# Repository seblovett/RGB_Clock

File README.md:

RGB_Clock
=========

A LED Clock

A contained PCB clock, with 60 RGB LEDs to display the time. 

Includes a noise sensor, LDR to adjust the brightness.

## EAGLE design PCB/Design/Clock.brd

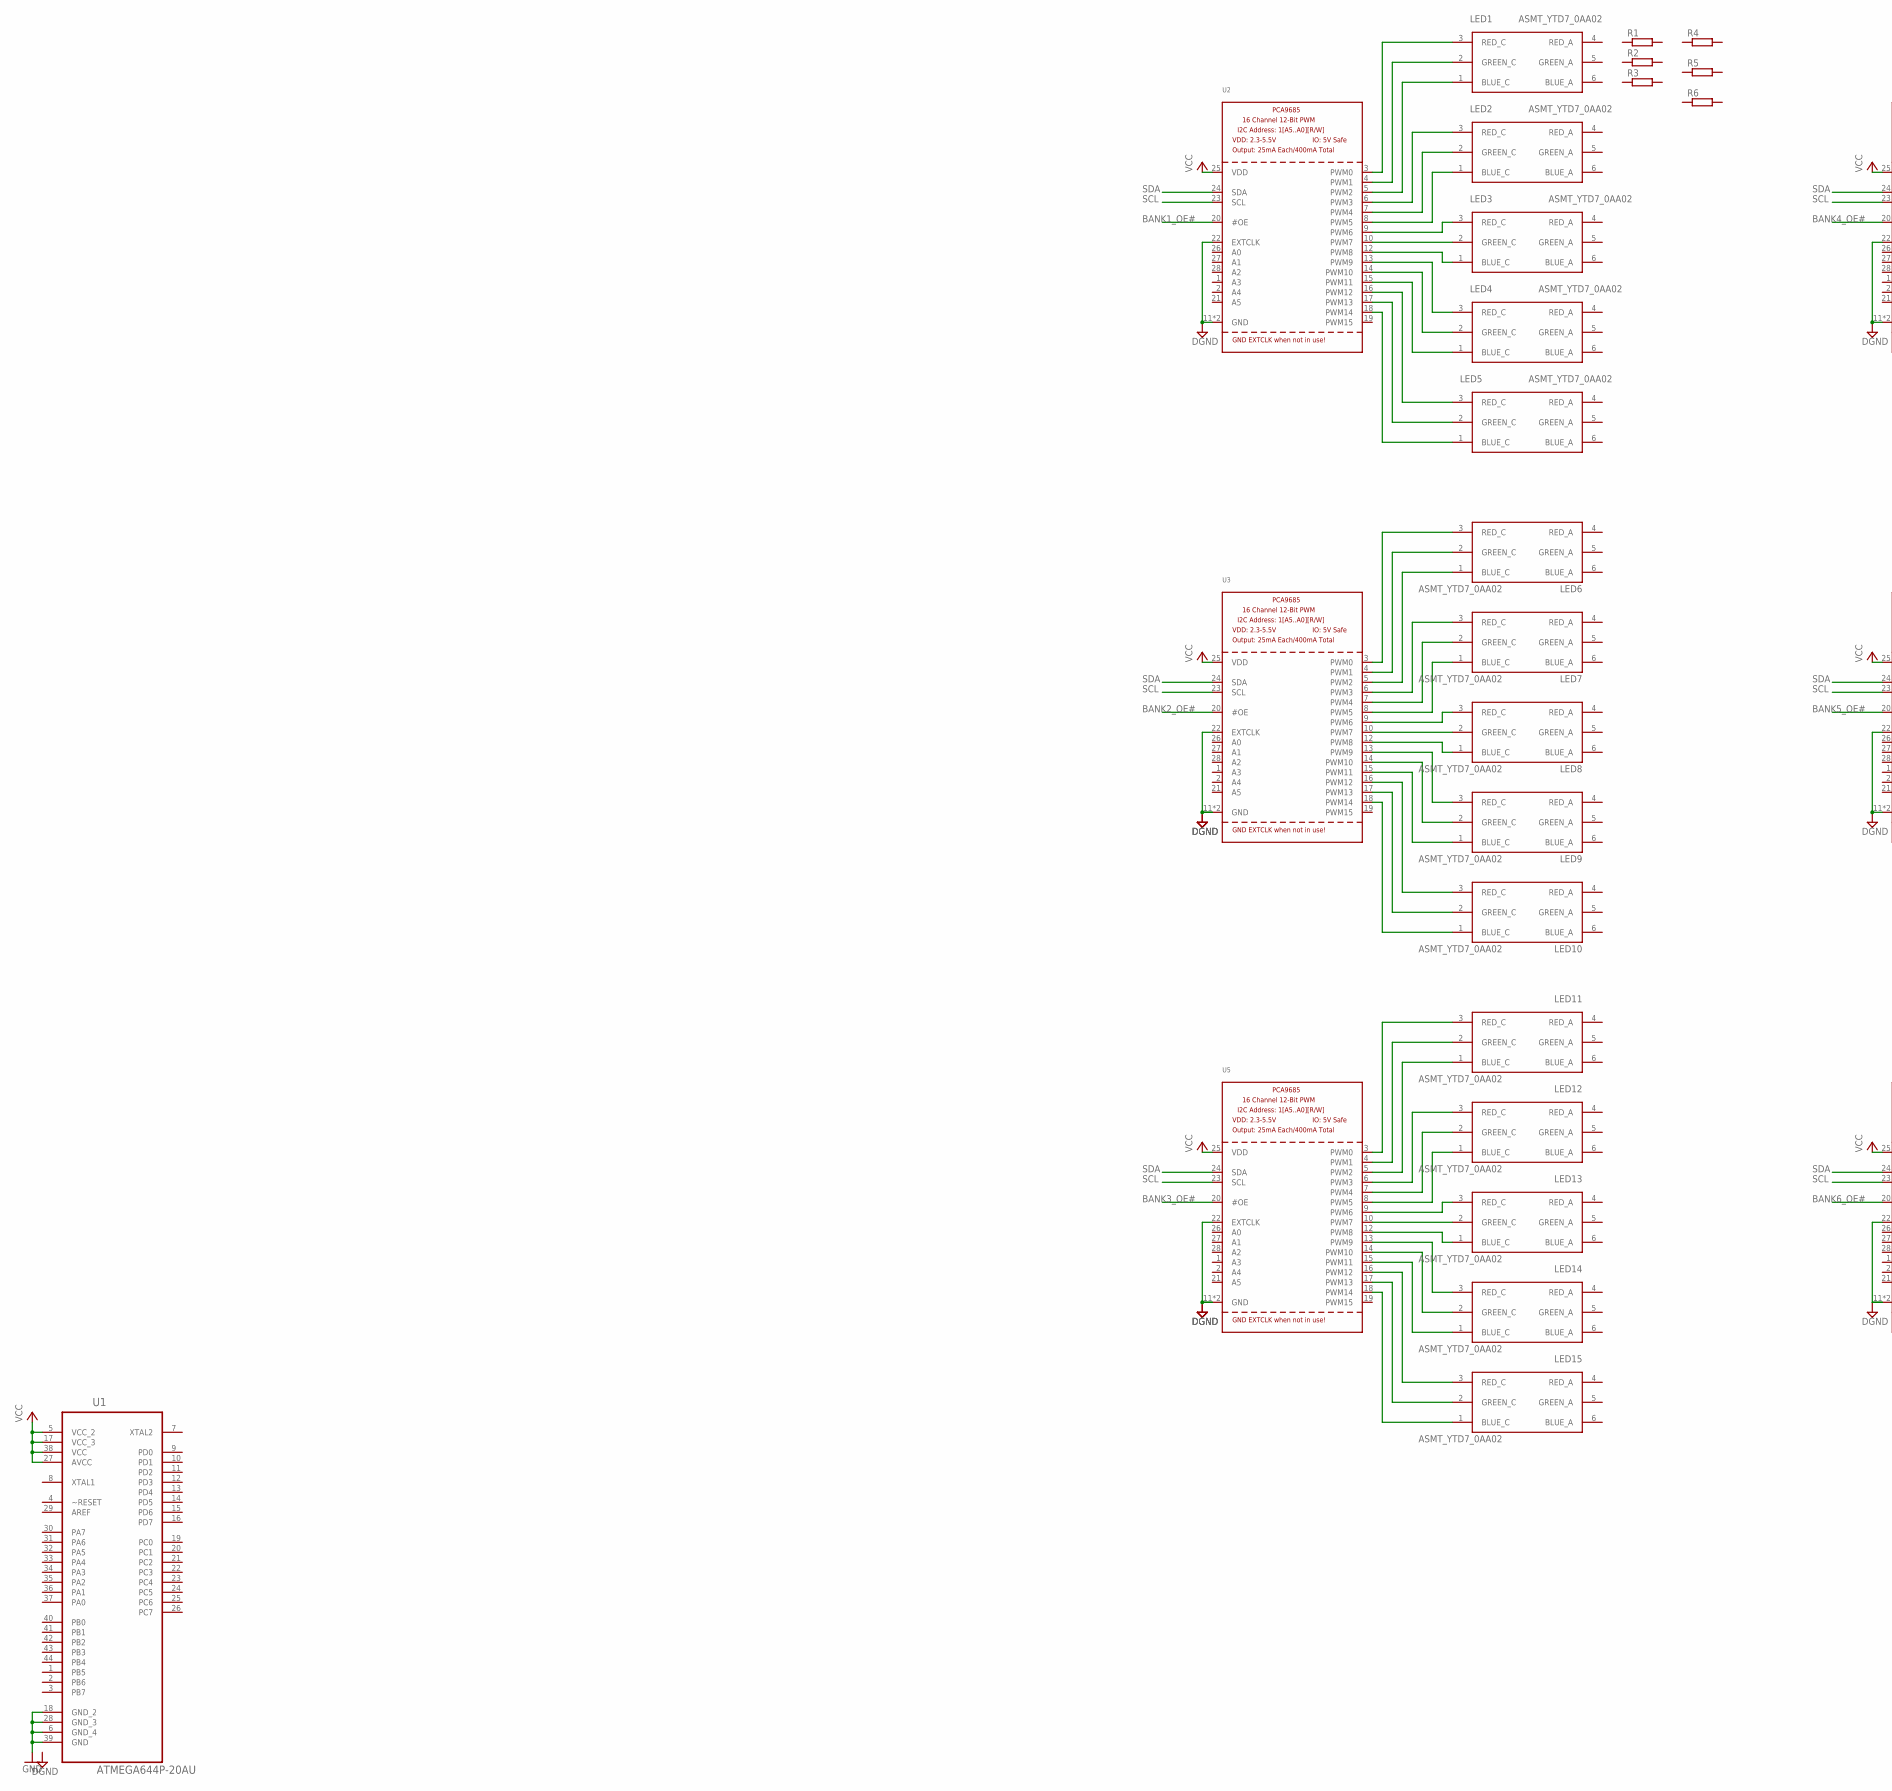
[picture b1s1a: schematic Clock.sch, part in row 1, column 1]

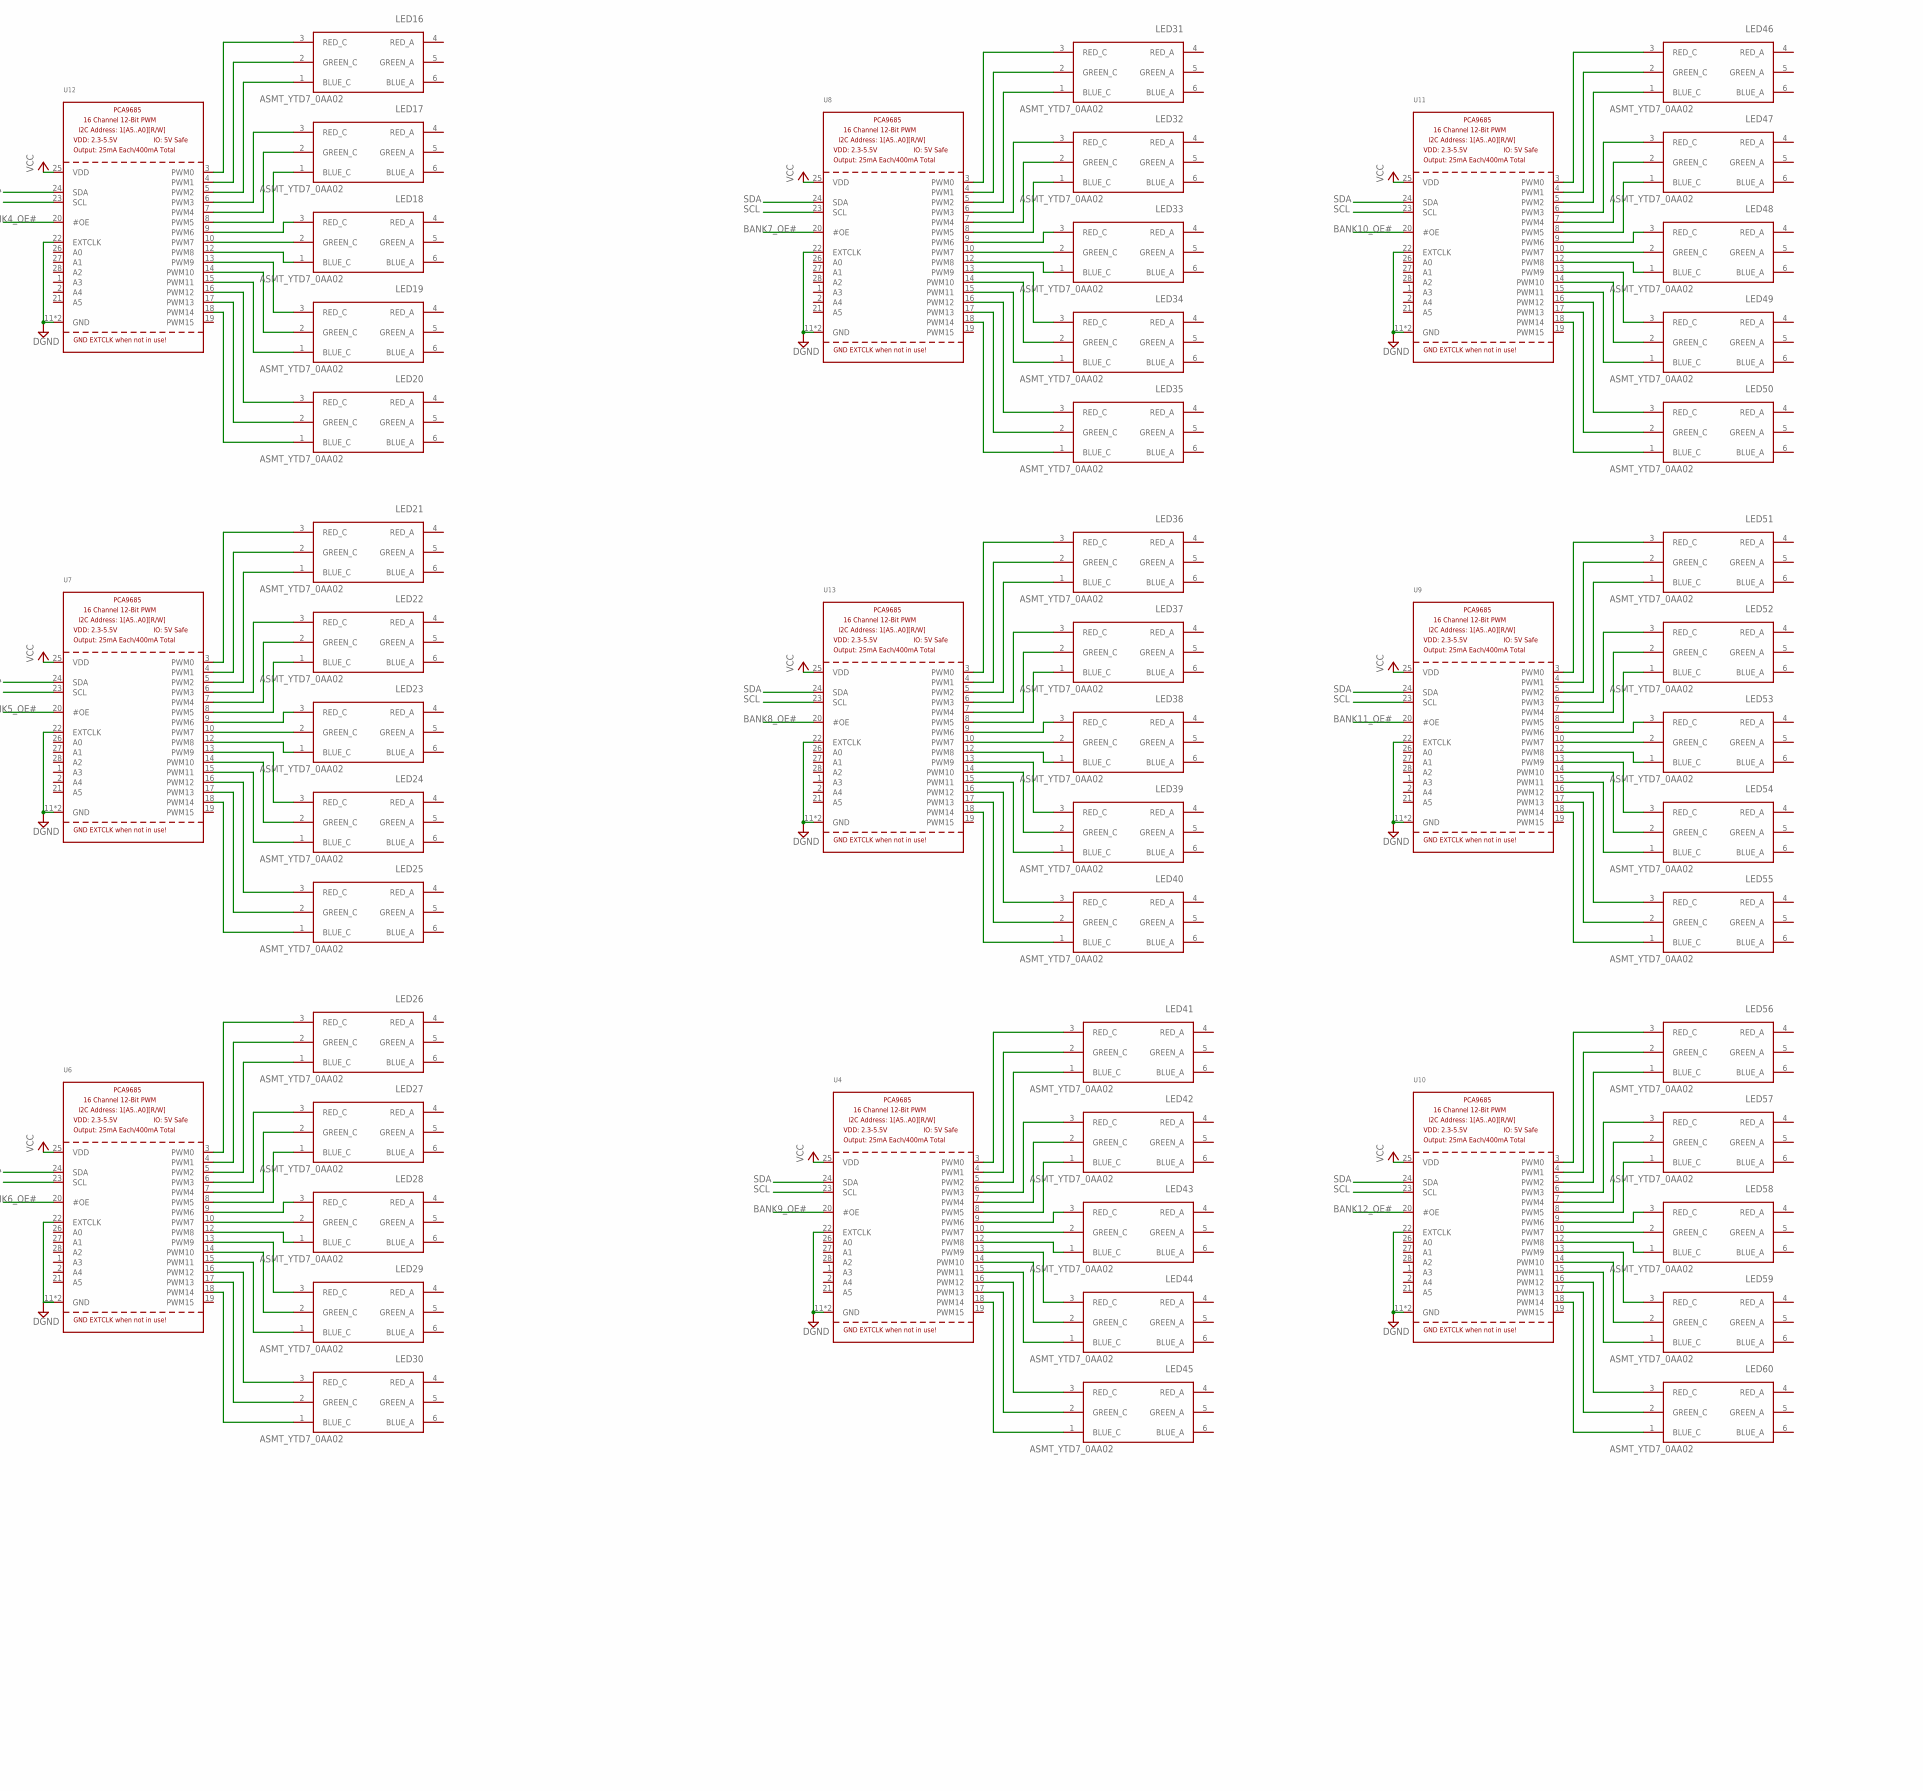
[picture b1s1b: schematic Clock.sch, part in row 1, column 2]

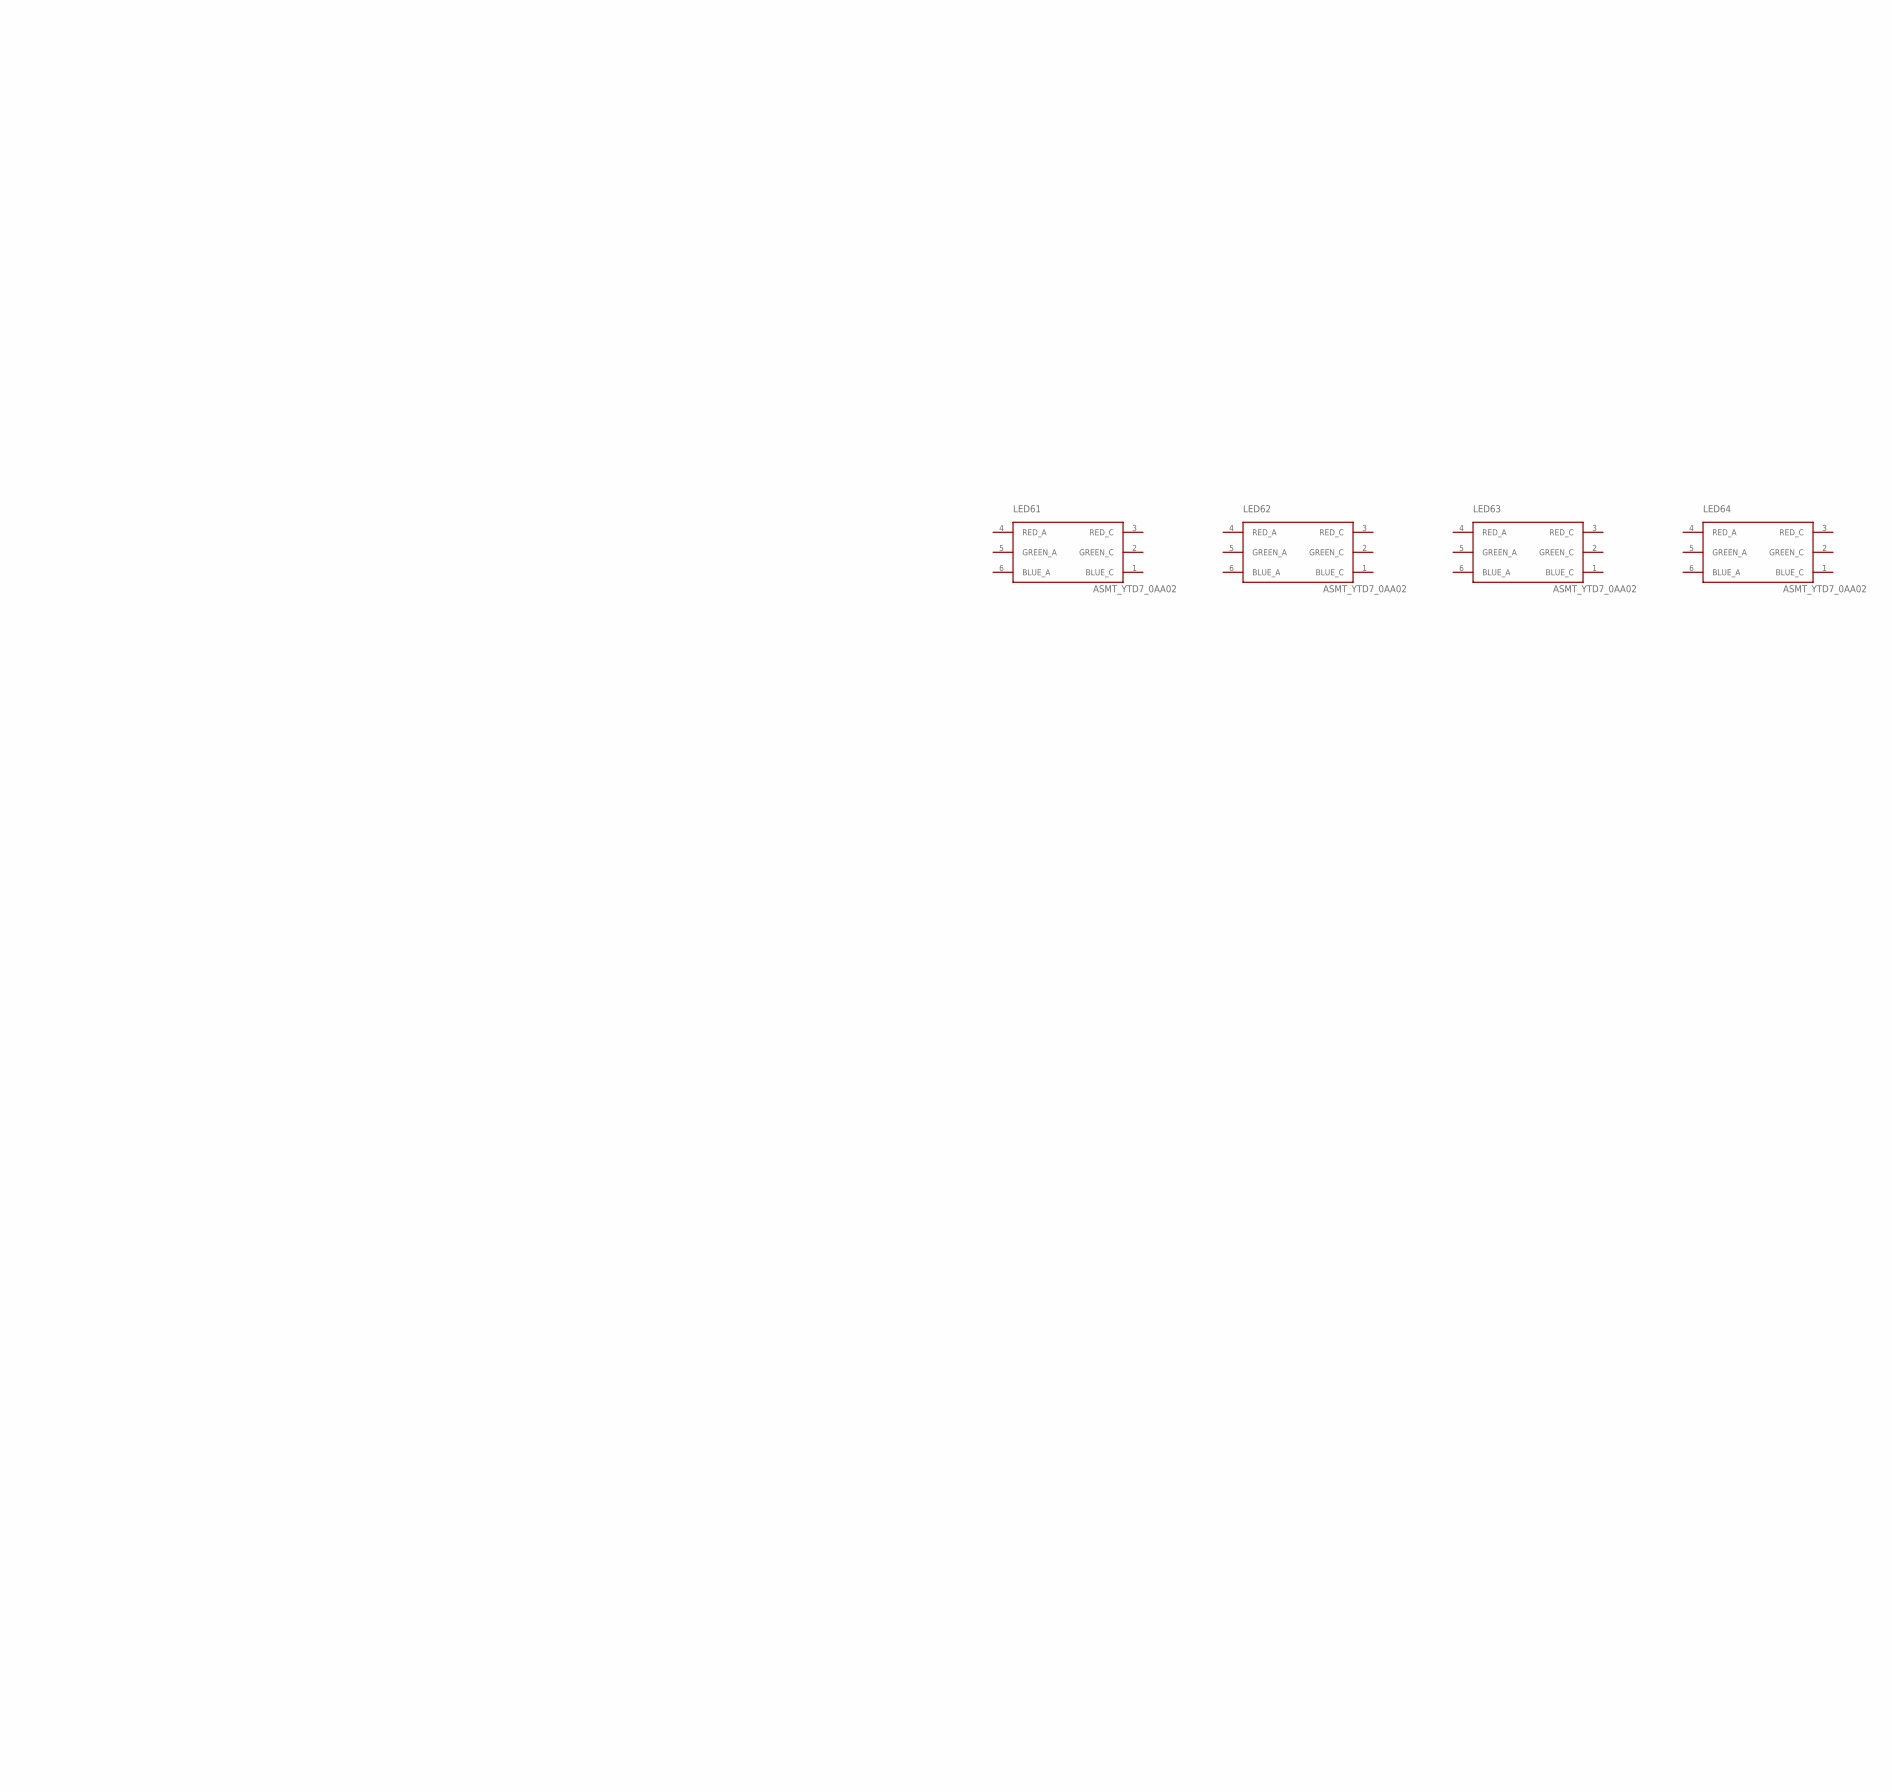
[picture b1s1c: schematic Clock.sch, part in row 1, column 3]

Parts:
LED1, LED2, LED3, LED4, LED5, LED6, LED7, LED8, LED9, LED10, LED11, LED12, LED13, LED14, LED15, LED16, LED17, LED18, LED19, LED20, LED21, LED22, LED23, LED24, LED25, LED26, LED27, LED28, LED29, LED30, LED31, LED32, LED33, LED34, LED35, LED36, LED37, LED38, LED39, LED40, LED41, LED42, LED43, LED44, LED45, LED46, LED47, LED48, LED49, LED50, LED51, LED52, LED53, LED54, LED55, LED56, LED57, LED58, LED59, LED60, LED61, LED62, LED63, LED64: ASMT_YTD7_0AA02; ASMT-YTD7-0AA02
R1, R2, R3: R0603
R4, R5, R6: R-EU_R0402; R0402
U1: ATMEGA644P-20AU; QFP80P1200X1200X120-44N
U2, U3, U4, U5, U6, U7, U8, U9, U10, U11, U12, U13: PCA9685QFN28; QFN28

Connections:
BANK1_OE#: U2.20 (#OE)
BANK2_OE#: U3.20 (#OE)
BANK3_OE#: U5.20 (#OE)
BANK4_OE#: U12.20 (#OE)
BANK5_OE#: U7.20 (#OE)
BANK6_OE#: U6.20 (#OE)
BANK7_OE#: U8.20 (#OE)
BANK8_OE#: U13.20 (#OE)
BANK9_OE#: U4.20 (#OE)
BANK10_OE#: U11.20 (#OE)
BANK11_OE#: U9.20 (#OE)
BANK12_OE#: U10.20 (#OE)
DGND: U2.11 (GND), U2.22 (EXTCLK), U2.M (GND), U3.11 (GND), U3.22 (EXTCLK), U3.M (GND), U4.11 (GND), U4.22 (EXTCLK), U4.M (GND), U5.11 (GND), U5.22 (EXTCLK), U5.M (GND), U6.11 (GND), U6.M (GND), U7.11 (GND), U7.22 (EXTCLK), U7.M (GND), U8.11 (GND), U8.22 (EXTCLK), U8.M (GND), U9.11 (GND), U9.22 (EXTCLK), U9.M (GND), U10.11 (GND), U10.22 (EXTCLK), U10.M (GND), U11.11 (GND), U11.22 (EXTCLK), U11.M (GND), U12.11 (GND), U12.22 (EXTCLK), U12.M (GND), U13.11 (GND), U13.22 (EXTCLK), U13.M (GND)
GND: U1.6 (GND_4), U1.18 (GND_2), U1.28 (GND_3), U1.39 (GND)
unnamed: LED8.3 (RED_C), U3.9 (PWM6)
unnamed: LED3.3 (RED_C), U2.9 (PWM6)
unnamed: LED3.1 (BLUE_C), U2.12 (PWM8)
unnamed: LED2.1 (BLUE_C), U2.8 (PWM5)
unnamed: LED2.2 (GREEN_C), U2.7 (PWM4)
unnamed: LED2.3 (RED_C), U2.6 (PWM3)
unnamed: LED1.1 (BLUE_C), U2.5 (PWM2)
unnamed: LED1.2 (GREEN_C), U2.4 (PWM1)
unnamed: LED1.3 (RED_C), U2.3 (PWM0)
unnamed: LED4.3 (RED_C), U2.13 (PWM9)
unnamed: LED4.2 (GREEN_C), U2.14 (PWM10)
unnamed: LED4.1 (BLUE_C), U2.15 (PWM11)
unnamed: LED5.3 (RED_C), U2.16 (PWM12)
unnamed: LED5.2 (GREEN_C), U2.17 (PWM13)
unnamed: LED5.1 (BLUE_C), U2.18 (PWM14)
unnamed: LED3.2 (GREEN_C), U2.10 (PWM7)
unnamed: LED8.1 (BLUE_C), U3.12 (PWM8)
unnamed: LED7.1 (BLUE_C), U3.8 (PWM5)
unnamed: LED7.2 (GREEN_C), U3.7 (PWM4)
unnamed: LED7.3 (RED_C), U3.6 (PWM3)
unnamed: LED6.1 (BLUE_C), U3.5 (PWM2)
unnamed: LED6.2 (GREEN_C), U3.4 (PWM1)
unnamed: LED6.3 (RED_C), U3.3 (PWM0)
unnamed: LED9.3 (RED_C), U3.13 (PWM9)
unnamed: LED9.2 (GREEN_C), U3.14 (PWM10)
unnamed: LED9.1 (BLUE_C), U3.15 (PWM11)
unnamed: LED10.3 (RED_C), U3.16 (PWM12)
unnamed: LED10.2 (GREEN_C), U3.17 (PWM13)
unnamed: LED10.1 (BLUE_C), U3.18 (PWM14)
unnamed: LED13.3 (RED_C), U5.9 (PWM6)
unnamed: LED13.1 (BLUE_C), U5.12 (PWM8)
unnamed: LED12.1 (BLUE_C), U5.8 (PWM5)
unnamed: LED12.2 (GREEN_C), U5.7 (PWM4)
unnamed: LED12.3 (RED_C), U5.6 (PWM3)
unnamed: LED11.1 (BLUE_C), U5.5 (PWM2)
unnamed: LED11.2 (GREEN_C), U5.4 (PWM1)
unnamed: LED11.3 (RED_C), U5.3 (PWM0)
unnamed: LED14.3 (RED_C), U5.13 (PWM9)
unnamed: LED14.2 (GREEN_C), U5.14 (PWM10)
unnamed: LED14.1 (BLUE_C), U5.15 (PWM11)
unnamed: LED15.3 (RED_C), U5.16 (PWM12)
unnamed: LED15.2 (GREEN_C), U5.17 (PWM13)
unnamed: LED15.1 (BLUE_C), U5.18 (PWM14)
unnamed: LED18.3 (RED_C), U12.9 (PWM6)
unnamed: LED18.1 (BLUE_C), U12.12 (PWM8)
unnamed: LED17.1 (BLUE_C), U12.8 (PWM5)
unnamed: LED17.2 (GREEN_C), U12.7 (PWM4)
unnamed: LED17.3 (RED_C), U12.6 (PWM3)
unnamed: LED16.1 (BLUE_C), U12.5 (PWM2)
unnamed: LED16.2 (GREEN_C), U12.4 (PWM1)
unnamed: LED16.3 (RED_C), U12.3 (PWM0)
unnamed: LED19.3 (RED_C), U12.13 (PWM9)
unnamed: LED19.2 (GREEN_C), U12.14 (PWM10)
unnamed: LED19.1 (BLUE_C), U12.15 (PWM11)
unnamed: LED20.3 (RED_C), U12.16 (PWM12)
unnamed: LED20.2 (GREEN_C), U12.17 (PWM13)
unnamed: LED20.1 (BLUE_C), U12.18 (PWM14)
unnamed: LED23.3 (RED_C), U7.9 (PWM6)
unnamed: LED23.1 (BLUE_C), U7.12 (PWM8)
unnamed: LED22.1 (BLUE_C), U7.8 (PWM5)
unnamed: LED22.2 (GREEN_C), U7.7 (PWM4)
unnamed: LED22.3 (RED_C), U7.6 (PWM3)
unnamed: LED21.1 (BLUE_C), U7.5 (PWM2)
unnamed: LED21.2 (GREEN_C), U7.4 (PWM1)
unnamed: LED21.3 (RED_C), U7.3 (PWM0)
unnamed: LED24.3 (RED_C), U7.13 (PWM9)
unnamed: LED24.2 (GREEN_C), U7.14 (PWM10)
unnamed: LED24.1 (BLUE_C), U7.15 (PWM11)
unnamed: LED25.3 (RED_C), U7.16 (PWM12)
unnamed: LED25.2 (GREEN_C), U7.17 (PWM13)
unnamed: LED25.1 (BLUE_C), U7.18 (PWM14)
unnamed: LED28.3 (RED_C), U6.9 (PWM6)
unnamed: LED28.1 (BLUE_C), U6.12 (PWM8)
unnamed: LED27.1 (BLUE_C), U6.8 (PWM5)
unnamed: LED27.2 (GREEN_C), U6.7 (PWM4)
unnamed: LED27.3 (RED_C), U6.6 (PWM3)
unnamed: LED26.1 (BLUE_C), U6.5 (PWM2)
unnamed: LED26.2 (GREEN_C), U6.4 (PWM1)
unnamed: LED26.3 (RED_C), U6.3 (PWM0)
unnamed: LED29.3 (RED_C), U6.13 (PWM9)
unnamed: LED29.2 (GREEN_C), U6.14 (PWM10)
unnamed: LED29.1 (BLUE_C), U6.15 (PWM11)
unnamed: LED30.3 (RED_C), U6.16 (PWM12)
unnamed: LED30.2 (GREEN_C), U6.17 (PWM13)
unnamed: LED30.1 (BLUE_C), U6.18 (PWM14)
unnamed: LED43.3 (RED_C), U4.9 (PWM6)
unnamed: LED43.1 (BLUE_C), U4.12 (PWM8)
unnamed: LED42.1 (BLUE_C), U4.8 (PWM5)
unnamed: LED42.2 (GREEN_C), U4.7 (PWM4)
unnamed: LED42.3 (RED_C), U4.6 (PWM3)
unnamed: LED41.1 (BLUE_C), U4.5 (PWM2)
unnamed: LED41.2 (GREEN_C), U4.4 (PWM1)
unnamed: LED41.3 (RED_C), U4.3 (PWM0)
unnamed: LED44.3 (RED_C), U4.13 (PWM9)
unnamed: LED44.2 (GREEN_C), U4.14 (PWM10)
unnamed: LED44.1 (BLUE_C), U4.15 (PWM11)
unnamed: LED45.3 (RED_C), U4.16 (PWM12)
unnamed: LED45.2 (GREEN_C), U4.17 (PWM13)
unnamed: LED45.1 (BLUE_C), U4.18 (PWM14)
unnamed: LED38.3 (RED_C), U13.9 (PWM6)
unnamed: LED38.1 (BLUE_C), U13.12 (PWM8)
unnamed: LED37.1 (BLUE_C), U13.8 (PWM5)
unnamed: LED37.2 (GREEN_C), U13.7 (PWM4)
unnamed: LED37.3 (RED_C), U13.6 (PWM3)
unnamed: LED36.1 (BLUE_C), U13.5 (PWM2)
unnamed: LED36.2 (GREEN_C), U13.4 (PWM1)
unnamed: LED36.3 (RED_C), U13.3 (PWM0)
unnamed: LED39.3 (RED_C), U13.13 (PWM9)
unnamed: LED39.2 (GREEN_C), U13.14 (PWM10)
unnamed: LED39.1 (BLUE_C), U13.15 (PWM11)
unnamed: LED40.3 (RED_C), U13.16 (PWM12)
unnamed: LED40.2 (GREEN_C), U13.17 (PWM13)
unnamed: LED40.1 (BLUE_C), U13.18 (PWM14)
unnamed: LED33.3 (RED_C), U8.9 (PWM6)
unnamed: LED33.1 (BLUE_C), U8.12 (PWM8)
unnamed: LED32.1 (BLUE_C), U8.8 (PWM5)
unnamed: LED32.2 (GREEN_C), U8.7 (PWM4)
unnamed: LED32.3 (RED_C), U8.6 (PWM3)
unnamed: LED31.1 (BLUE_C), U8.5 (PWM2)
unnamed: LED31.2 (GREEN_C), U8.4 (PWM1)
unnamed: LED31.3 (RED_C), U8.3 (PWM0)
unnamed: LED34.3 (RED_C), U8.13 (PWM9)
unnamed: LED34.2 (GREEN_C), U8.14 (PWM10)
unnamed: LED34.1 (BLUE_C), U8.15 (PWM11)
unnamed: LED35.3 (RED_C), U8.16 (PWM12)
unnamed: LED35.2 (GREEN_C), U8.17 (PWM13)
unnamed: LED35.1 (BLUE_C), U8.18 (PWM14)
unnamed: LED48.3 (RED_C), U11.9 (PWM6)
unnamed: LED48.1 (BLUE_C), U11.12 (PWM8)
unnamed: LED47.1 (BLUE_C), U11.8 (PWM5)
unnamed: LED47.2 (GREEN_C), U11.7 (PWM4)
unnamed: LED47.3 (RED_C), U11.6 (PWM3)
unnamed: LED46.1 (BLUE_C), U11.5 (PWM2)
unnamed: LED46.2 (GREEN_C), U11.4 (PWM1)
unnamed: LED46.3 (RED_C), U11.3 (PWM0)
unnamed: LED49.3 (RED_C), U11.13 (PWM9)
unnamed: LED49.2 (GREEN_C), U11.14 (PWM10)
unnamed: LED49.1 (BLUE_C), U11.15 (PWM11)
unnamed: LED50.3 (RED_C), U11.16 (PWM12)
unnamed: LED50.2 (GREEN_C), U11.17 (PWM13)
unnamed: LED50.1 (BLUE_C), U11.18 (PWM14)
unnamed: LED53.3 (RED_C), U9.9 (PWM6)
unnamed: LED53.1 (BLUE_C), U9.12 (PWM8)
unnamed: LED52.1 (BLUE_C), U9.8 (PWM5)
unnamed: LED52.2 (GREEN_C), U9.7 (PWM4)
unnamed: LED52.3 (RED_C), U9.6 (PWM3)
unnamed: LED51.1 (BLUE_C), U9.5 (PWM2)
unnamed: LED51.2 (GREEN_C), U9.4 (PWM1)
unnamed: LED51.3 (RED_C), U9.3 (PWM0)
unnamed: LED54.3 (RED_C), U9.13 (PWM9)
unnamed: LED54.2 (GREEN_C), U9.14 (PWM10)
unnamed: LED54.1 (BLUE_C), U9.15 (PWM11)
unnamed: LED55.3 (RED_C), U9.16 (PWM12)
unnamed: LED55.2 (GREEN_C), U9.17 (PWM13)
unnamed: LED55.1 (BLUE_C), U9.18 (PWM14)
unnamed: LED58.3 (RED_C), U10.9 (PWM6)
unnamed: LED58.1 (BLUE_C), U10.12 (PWM8)
unnamed: LED57.1 (BLUE_C), U10.8 (PWM5)
unnamed: LED57.2 (GREEN_C), U10.7 (PWM4)
unnamed: LED57.3 (RED_C), U10.6 (PWM3)
unnamed: LED56.1 (BLUE_C), U10.5 (PWM2)
unnamed: LED56.2 (GREEN_C), U10.4 (PWM1)
unnamed: LED56.3 (RED_C), U10.3 (PWM0)
unnamed: LED59.3 (RED_C), U10.13 (PWM9)
unnamed: LED59.2 (GREEN_C), U10.14 (PWM10)
unnamed: LED59.1 (BLUE_C), U10.15 (PWM11)
unnamed: LED60.3 (RED_C), U10.16 (PWM12)
unnamed: LED60.2 (GREEN_C), U10.17 (PWM13)
unnamed: LED60.1 (BLUE_C), U10.18 (PWM14)
unnamed: LED48.2 (GREEN_C), U11.10 (PWM7)
unnamed: LED53.2 (GREEN_C), U9.10 (PWM7)
unnamed: LED58.2 (GREEN_C), U10.10 (PWM7)
unnamed: LED43.2 (GREEN_C), U4.10 (PWM7)
unnamed: LED38.2 (GREEN_C), U13.10 (PWM7)
unnamed: LED33.2 (GREEN_C), U8.10 (PWM7)
unnamed: LED18.2 (GREEN_C), U12.10 (PWM7)
unnamed: LED23.2 (GREEN_C), U7.10 (PWM7)
unnamed: LED28.2 (GREEN_C), U6.10 (PWM7)
unnamed: LED13.2 (GREEN_C), U5.10 (PWM7)
unnamed: LED8.2 (GREEN_C), U3.10 (PWM7)
SCL: U2.23 (SCL), U3.23 (SCL), U4.23 (SCL), U5.23 (SCL), U6.23 (SCL), U7.23 (SCL), U8.23 (SCL), U9.23 (SCL), U10.23 (SCL), U11.23 (SCL), U12.23 (SCL), U13.23 (SCL)
SDA: U2.24 (SDA), U3.24 (SDA), U4.24 (SDA), U5.24 (SDA), U6.24 (SDA), U7.24 (SDA), U8.24 (SDA), U9.24 (SDA), U10.24 (SDA), U11.24 (SDA), U12.24 (SDA), U13.24 (SDA)
VCC: U1.5 (VCC_2), U1.17 (VCC_3), U1.27 (AVCC), U1.38 (VCC), U2.25 (VDD), U3.25 (VDD), U4.25 (VDD), U5.25 (VDD), U6.25 (VDD), U7.25 (VDD), U8.25 (VDD), U9.25 (VDD), U10.25 (VDD), U11.25 (VDD), U12.25 (VDD), U13.25 (VDD)

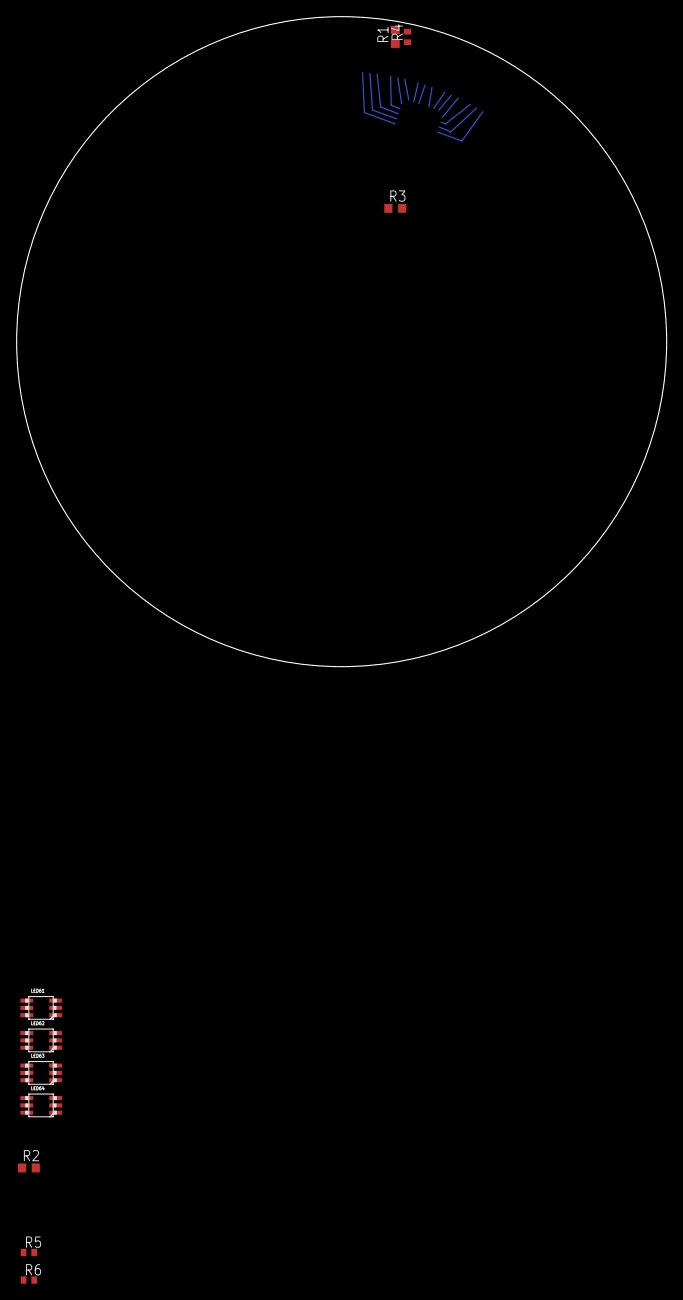
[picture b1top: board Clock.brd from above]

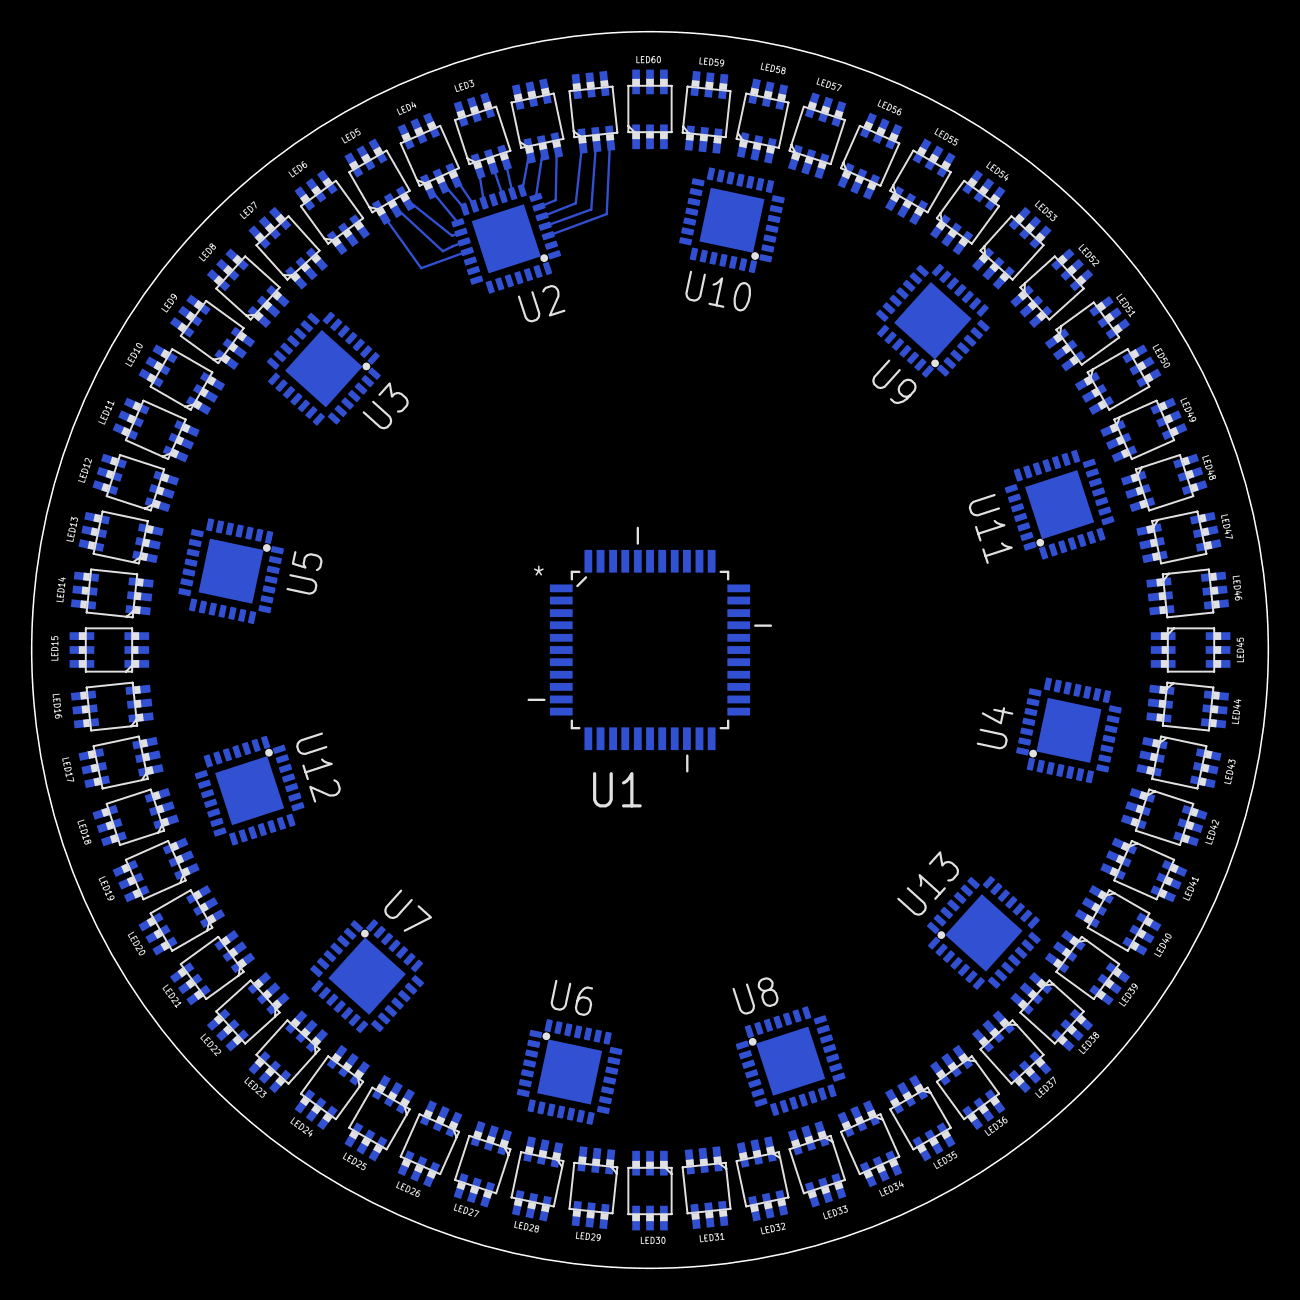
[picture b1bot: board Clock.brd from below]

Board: 2 copper layers, 80.0 x 80.0 mm, 83 parts (73 on the bottom side), 185 nets.

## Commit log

2014-12-29 Added datasheets
2014-12-29 Added base design. Much to do!
2014-12-29 Ignore shtuff
2014-12-29 Some useful tings to generate long commands for placing LEDs in the right place
2014-12-30 connected all PWM and LEDs.
2014-12-30 Probably joined with last commit..
2015-01-10 Redone schematics in KiCAD.
    Need to sort out ref des' for LEDs and PWM drivers and then can begin some layout!
2015-01-10 LEDs are placed!
    Worked out how to script KiCAD to do it too. Winner winner, time for a chicken dinner
2015-01-14 Latest schematics and pcb.
2015-01-14 Removed old EAGLE stuff.
2015-01-14 Added all CAD files
2015-01-14 Added libraries
2015-01-14 Updated script. Moves the PWM ICs also
2015-01-14 Added schematic lib
2015-01-14 Removed back up file
2015-01-27 Updated schematics
2015-01-27 Removed RF. Placed all LED drivers and passives and begun routing
2015-01-27 Corrected part
2015-01-28 Added power in connector in schematics. #3
2015-01-28 Added some switches for interface #7
2015-01-28 Changed to TSSOP package
2015-01-28 Changed lots
    Finalised the Inductor. Closes #5
    Changed USB Connector. Closes #4
    Added four switches for a simple interface. Closes #7
    Added a power jack. Closes #3
    Found RTC Oscillator. Closes #1.
    Added part numbers to all major components. Closes #2
2015-01-29 Ammended a net. Done a lot of routing
2015-01-30 Done lots of routing. Mostly done.
    Rearranged some connections to make routing easier.
    Need to check unconnected nets.
2015-02-01 Main GND plane added.
    Need to add island plane for SMPS
2015-02-01 Sorted SMPS ground plane
2015-02-01 Sorted silkscreen out. Added a select to change function of one of the switches to between a reset or a general purpose
2015-02-01 Added some libs
2015-02-01 Added the datasheet for the ATXMega used
2015-02-01 Added SMPS related things
2015-02-01 Updated git ignore
2015-02-01 Added clock face to silkscreen
2015-02-09 Completed layout of 10cm board. Fixes #8
2015-02-09 added some more datasheets
2015-02-09 Added BoM with costings.
    Also added schematic and layout review
2015-03-23 Started Redesign.
2015-03-25 Done some more layout.
    Need to sort pin swaps for the OE lines and complete routing
2015-04-03 Split design into two modules
2015-04-05 Added some debug headers for power and UART
    Added silkscreen info also.
2015-04-05 Sorted silkscreen out and panelized design.
2015-05-10 Added startings of AVR Code base
2015-05-10 Added C temp files to ignore
2015-05-12 sTUFF
2015-05-31 Lots of code. Still need to get RTC working.

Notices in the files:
parts and their libraries:
microbuilder: This work is placed in the public domain, and may be freely used for commercial and non-commercial work with the following conditions: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
